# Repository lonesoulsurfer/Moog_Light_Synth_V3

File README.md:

# Moog Light Synth V3

This synth has a pulse-width-modulated (PWM) oscillator and a light-controlled resonant low-pass filter. You play it with light, on two light-dependent resistors (LDRs), and with 13 keys.

## Build guide and video

- Step-by-step build guide on Instructables: [Moog Light Synth V3](https://www.instructables.com/Moog-Light-Synth-V3/)
- Video on YouTube: [Moog Light Synth V3](https://www.youtube.com/watch?v=9Q7pgyfTjew)

## Features

- PWM oscillator with a "growling" sound, through a high-resonance low-pass filter
- 2 LDRs control the oscillator
- 13 keys: play it as a 1-octave keyboard
- 2 drone oscillators (40106 hex inverter), which you can switch off. Thus there are 3 oscillators in total.
- Echo and reverb module, changed to add feedback
- Arpeggiator
- You can also play it with one potentiometer and the LDRs only

## What you need

- The Gerber files for the PCB are in `Moog Light Synth V3 - Gerber Files.zip`. You can send them to a PCB maker.
- All parts are in the parts list (`Moog Light Synth V3 - Parts List.xlsx`).

## Build it

The Instructables guide shows each step, with photos. In short:

1. Send the Gerber files to a PCB maker.
2. Get the parts in the parts list.
3. Solder the parts to the PCB.
4. Connect the power and test the circuit.

## Files in this repository

| Folder or file | Contents |
|----------------|----------|
| `Moog Light Synth V3 - Gerber Files.zip` | Gerber files for the PCB, ready to order |
| `Eagle Schematic and Board/` | Eagle files for the PCB |
| `Front Panel/` | Front panel design (SVG and PDF) |
| `Moog Light Synth V3 - Parts List.xlsx` | Parts list |

## Support

Do you like this project? You can support my work on [GitHub Sponsors](https://github.com/sponsors/lonesoulsurfer).

## Licence

This project uses the [CERN Open Hardware Licence v2, Strongly Reciprocal](LICENSE) (CERN-OHL-S-2.0). Copyright (c) 2025 Marcus (lonesoulsurfer).

You can make, change and sell boards from these files. If you share or sell a changed design, you must also share the changed design files under the same licence.

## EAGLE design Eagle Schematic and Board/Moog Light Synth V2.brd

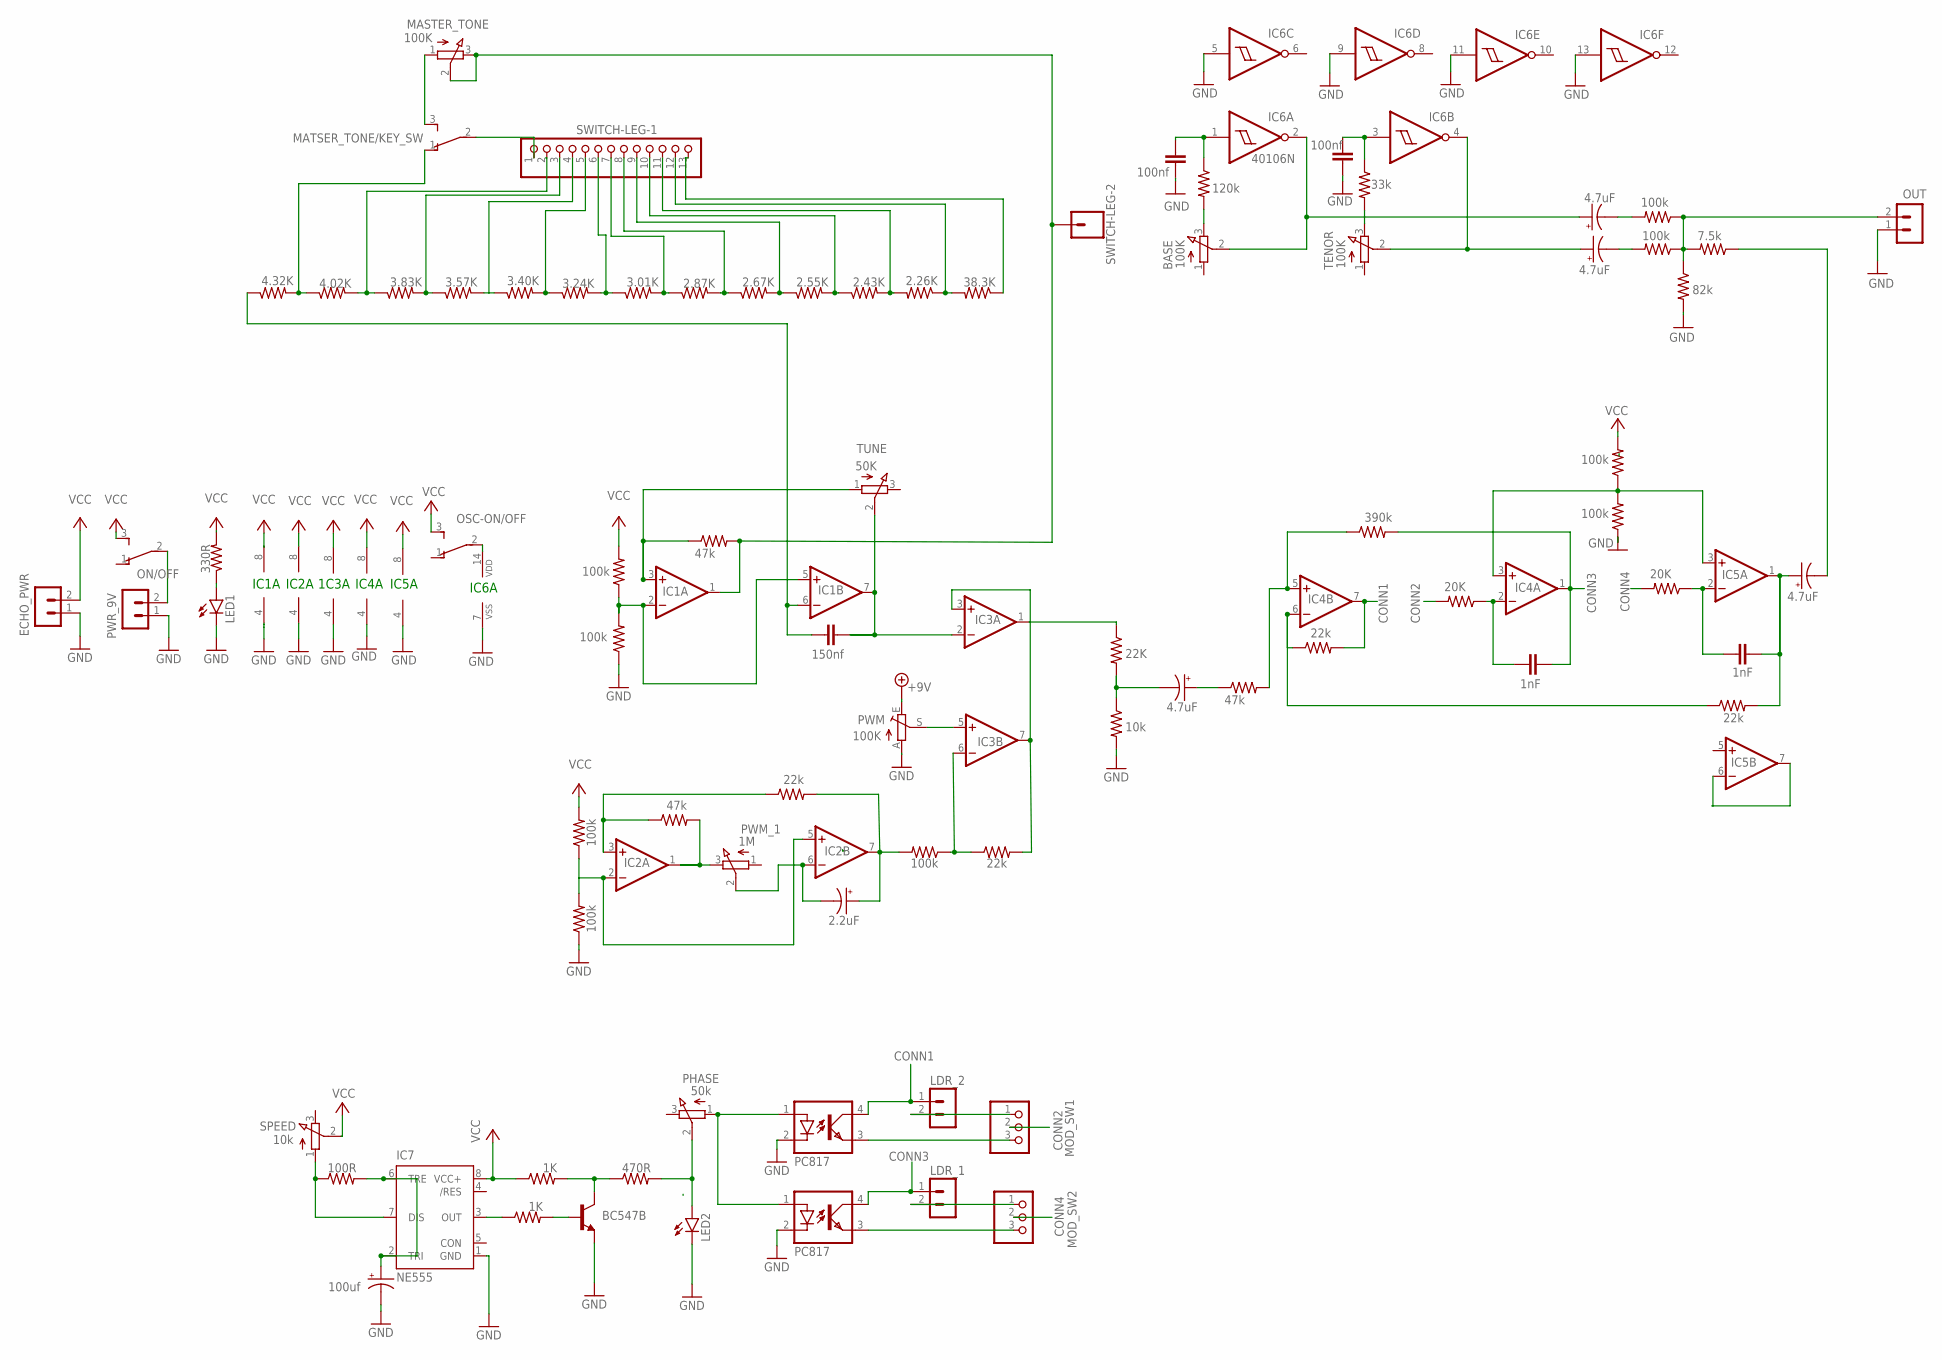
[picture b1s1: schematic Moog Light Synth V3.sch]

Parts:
BASE: 100K; EVUF
C1: 150nf; C050-024X044
C2: 2.2uF; E2,5-5
C3, C6, C8, C9: 4.7uF; E2,5-5
C4, C5: 1nF; C050-024X044
C7, C10: 100nf; C050-024X044
C11: 100uf; E2,5-5
ECHO_PWR: B2B-PH-K-S
IC1, IC2, IC3, IC4, IC5: LM358N; DIL08
IC6: 40106N; DIL14
IC7: NE555; DIL-08
LDR_1, LDR_2: B2B-PH-K-S
LED1, LED2: LED5MM
MASTER_TONE: 100K; EVUF
MATSER_TONE/KEY_SW: TL36PO; TL3XPO
MOD_SW1, MOD_SW2: PINHD-1X3; 1X03
OK1, OK3: PC817; DIL04
ON/OFF: TL36PO; TL3XPO
OSC-ON/OFF: TL36PO; TL3XPO
OUT: B2B-PH-K-S
PHASE: 50k; EVUF
PWM: 100K; B25P
PWM_1: 1M; EVUF
PWR_9V: B2B-PH-K-S
Q1: BC547B; TO92
R1, R2, R3, R4, R7, R15, R19, R23, R24: 100k; 0207/10
R5, R12, R16: 47k; 0207/10
R6, R20: 20K; 0207/10
R8, R13, R18, R21: 22k; 0207/10
R9: 120k; 0207/10
R10: 10k; 0207/10
R11: 22K; 0207/10
R14: 390k; 0207/10
R22: 33k; 0207/10
R25: 82k; 0207/10
R26: 7.5k; 0207/10
R27: 4.02K; 0207/10
R28: 3.83K; 0207/10
R29: 3.57K; 0207/10
R30: 3.40K; 0207/10
R31: 3.24K; 0207/10
R32: 3.01K; 0207/10
R33: 2.87K; 0207/10
R34: 4.32K; 0207/10
R35: 2.67K; 0207/10
R36: 2.55K; 0207/10
R37: 330R; 0207/10
R38: 100R; 0207/10
R39, R41: 1K; 0207/10
R40: 470R; 0207/10
R42: 2.43K; 0207/10
R43: 2.26K; 0207/10
R44: 38.3K; 0207/10
SPEED: 10k; EVUF
SWITCH-LEG-1: PINHD-1X13; 1X13
SWITCH-LEG-2: CONN_01; 1X01
TENOR: 100K; EVUF
TUNE: 50K; EVUF

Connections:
4: LDR_1.2, MOD_SW2.1
CONN1: IC4.7 (OUT), LDR_2.1, OK1.4 (COL), R13.2
CONN2: MOD_SW1.2, R6.2
CONN3: C4.2, IC4.1 (OUT), LDR_1.1, OK3.4 (COL), R14.2
CONN4: MOD_SW2.2, R20.2
GND: C7.1, C10.1, C11.-, ECHO_PWR.1, IC1.4 (V-), IC2.4 (V-), IC3.4 (V-), IC4.4 (V-), IC5.4 (V-), IC6.5 (I), IC6.7 (VSS), IC6.9 (I), IC6.11 (I), IC6.13 (I), IC7.1 (GND), LED1.K (C), LED2.K (C), OK1.2 (C), OK3.2 (C), OUT.1, PWM.A, PWR_9V.1, Q1.1 (E), R2.1, R3.1, R10.2, R19.1, R25.2
unnamed: IC1.3 (+IN), R5.1, TUNE.1 (A)
unnamed: C1.1, IC1.6 (-IN), R34.1
unnamed: IC1.2 (-IN), IC1.5 (+IN), R1.1, R2.2
unnamed: C1.2, IC1.7 (OUT), IC3.2 (-IN), TUNE.2 (S)
unnamed: OK1.1 (A), OK3.1 (A), PHASE.1 (A)
unnamed: IC2.2 (-IN), IC2.5 (+IN), R3.2, R4.1
unnamed: IC2.3 (+IN), R16.1, R18.1
unnamed: IC2.1 (OUT), PWM_1.3 (E), R16.2
unnamed: C2.-, IC2.6 (-IN), PWM_1.2 (S)
unnamed: C2.+, IC2.7 (OUT), R7.2, R18.2
unnamed: IC3.6 (-IN), R7.1, R8.1
unnamed: IC3.3 (+IN), IC3.7 (OUT), R8.2
unnamed: IC3.5 (+IN), PWM.S
unnamed: IC3.1 (OUT), R11.1
unnamed: C3.-, R10.1, R11.2
unnamed: C3.+, R12.1
unnamed: IC4.5 (+IN), R12.2, R14.1
unnamed: IC4.6 (-IN), R13.1, R21.1
unnamed: R28.2, R29.1, SWITCH-LEG-1.3
unnamed: R42.2, R43.2, SWITCH-LEG-1.11
unnamed: MATSER_TONE/KEY_SW.1 (O), R27.1, R34.2
unnamed: C4.1, IC4.2 (-IN), R6.1
unnamed: IC4.3 (+IN), IC5.3 (+IN), R15.1, R19.2
unnamed: R22.2, TENOR.3 (E)
unnamed: C5.1, IC5.2 (-IN), R20.1
unnamed: C5.2, C6.+, IC5.1 (OUT), R21.2
unnamed: IC5.6 (-IN), IC5.7 (OUT)
unnamed: C7.2, IC6.1 (I), R9.1
unnamed: BASE.3 (E), R9.2
unnamed: BASE.2 (S), C8.+, IC6.2 (O)
unnamed: C10.2, IC6.3 (I), R22.1
unnamed: R44.1, SWITCH-LEG-1.13
unnamed: C9.+, IC6.4 (O), TENOR.2 (S)
unnamed: C8.-, R23.2
unnamed: C9.-, R24.2
unnamed: C6.-, R26.1
unnamed: OUT.2, R23.1, R24.1, R25.1, R26.2
unnamed: R30.2, R31.1, SWITCH-LEG-1.5
unnamed: R32.2, R33.1, SWITCH-LEG-1.7
unnamed: MATSER_TONE/KEY_SW.2, SWITCH-LEG-1.1
unnamed: MASTER_TONE.1 (A), MATSER_TONE/KEY_SW.3 (S)
unnamed: R36.2, R42.1, SWITCH-LEG-1.10
unnamed: R27.2, R28.1, SWITCH-LEG-1.2
unnamed: R31.2, R32.1, SWITCH-LEG-1.6
unnamed: IC6.14 (VDD), OSC-ON/OFF.2
unnamed: R33.2, R35.1, SWITCH-LEG-1.8
unnamed: R35.2, R36.1, SWITCH-LEG-1.9
unnamed: IC1.1 (OUT), MASTER_TONE.2 (S), MASTER_TONE.3 (E), R5.2, SWITCH-LEG-2.1
unnamed: R29.2, R30.1, SWITCH-LEG-1.4
unnamed: LED1.A, R37.1
unnamed: ON/OFF.2, PWR_9V.2
unnamed: LED2.A, PHASE.2 (S), R40.2
unnamed: C11.+, IC7.2 (TRI), IC7.6 (TRE), R38.2
unnamed: IC7.7 (DIS), R38.1, SPEED.1 (A)
unnamed: Q1.3 (C), R40.1, R41.2
unnamed: IC7.3 (OUT), R39.1
unnamed: Q1.2 (B), R39.2
unnamed: R43.1, R44.2, SWITCH-LEG-1.12
unnamed: MOD_SW1.3, OK1.3 (EMIT)
unnamed: MOD_SW2.3, OK3.3 (EMIT)
unnamed: LDR_2.2, MOD_SW1.1
VCC: ECHO_PWR.2, IC1.8 (V+), IC2.8 (V+), IC3.8 (V+), IC4.8 (V+), IC5.8 (V+), IC7.8 (VCC+), ON/OFF.3 (S), OSC-ON/OFF.3 (S), PWM.E, R1.2, R4.2, R15.2, R37.2, R41.1, SPEED.2 (S)

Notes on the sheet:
IC1A
1C3A
IC2A
IC4A
IC5A
IC6A

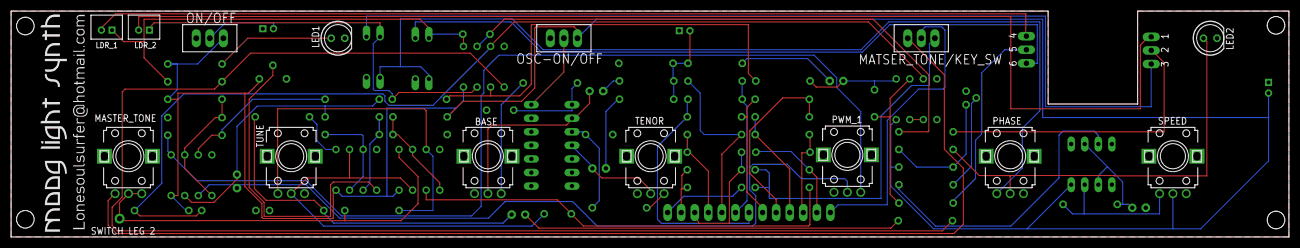
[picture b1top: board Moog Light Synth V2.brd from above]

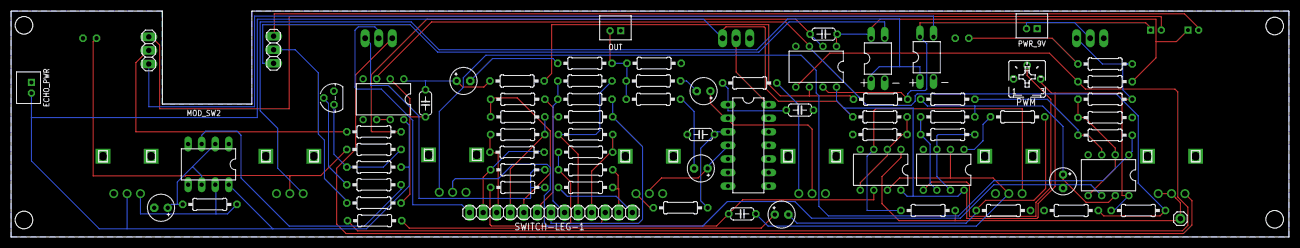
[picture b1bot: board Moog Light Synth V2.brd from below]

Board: 2 copper layers, 239.3 x 42.3 mm, 86 parts (72 on the bottom side), 68 nets.

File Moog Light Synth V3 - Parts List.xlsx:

Part | Type | Value | Qty | Notes | Links
Capacitor | Polyester | 150nf | 1
 |  | 1nf | 2
 |  | 100nf | 3
 | Polarized | 2.2uf | 1
 |  | 4.7uf | 4
Potentiometer | EVUF2A (vertical, through hole type) | 100K | 3
 |  | 50K | 2
 |  | 1M | 1
 |  | 10K | 1
 | Trimmer | 100K | 1
IC's | LM358 |  | 5
 | 40106 |  | 1
 | 555 |  | 1
Light Dependent Resistor (LDR) |  |  | 4
LED | 5mm |  | 4
SPDT Switch | Toggle - through hole type |  | 3
DPDT Switch | Toggle |  | 1
JST Connector | Micro |  | 3
Transistor | BC547 |  | 1
Vactrols |  |  | 2 | I made my own using LED's and LDR's. I find that these work better than Optocou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
Resistors | Metal Film | 100K | 10
 |  | 47K | 3
 |  | 20K | 2
 |  | 22K | 5
 |  | 120K | 1
 |  | 10K | 1
 |  | 390K | 1
 |  | 33K | 1
 |  | 82K | 1
 |  | 7.5K | 1
 |  | 4.02K | 1 | These resistors make up the resistor ladder for the keys. You can either use va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
 |  | 3.83K | 1
 |  | 3.57K | 1
 |  | 3.40K | 1
 |  | 3.24K | 1
 |  | 3.01K | 1
 |  | 2.87K | 1
 |  | 4.32K | 1
 |  | 2.67K | 1
 |  | 2.55K | 1
 |  | 2.43K | 1
 |  | 2.26K | 1
 |  | 38.3K | 1
Echo/Reverb Module
Part | Type | Value | Qty | Notes
Potentiometer |  | 50K | 2
 |  | 1M | 1

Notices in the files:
parts and their libraries:
SparkFun-Connectors: Licensing: Creative Commons ShareAlike 4.0 International - https://creativecommons.org/licenses/by-sa/4.0
